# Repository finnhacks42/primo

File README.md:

KinderBot
=====

Contains design files and code for my version of the Primo robotic platform for young kids www.primo.io licenced under CC by-nc-sa 4.0 International
## Components
### Board
   - laser cut xxx and yyy in 3mm ply or bamboo
   - laser cut zzz in 1.5mm clear acrylic
   - 3d print 4 off zzz
   - 1 colorsense PCB
   - Arduino mega
   - HC05 serial bluetooth module
   - 16 rgb leds
   - 16 red leds

### Robot
   - Kinder surprise egg
   - laser cut zzz of 3mm ply
   - Arduino pro micro 
   - 2 gear motors 3-6V with tyres
   - HC05 serial bluetooth module
   - H-Bridge IC (sn75441one)
   - 1.1K resistor
   - 1.2K resistor
   - 2 12pin female header
   - 2 2pin male header
   - Battery holder for 4xAA

## Pairing Bluetooth modules
Once you have all your components ready, the first step set up the two HC-05 bluetooth modules to automatically pair with one another when they are turned on. We do this now as it is easier to setup and debug with both Arduinos handy than when they are plugged into the board/robot. We will configure the module for the board as the master and the module for the robot as the slave. 

   1) Get a permanent marker and write S for slave on one module and M for master on the other. Do it now, trust me, otherwise you will configure them and then forget which is which.
   2) Using the Arduino pro-micro for your bot, construct the circuit below on a breadboard.

Note that different manufacturers of the HC-05 breakout boards have used slightly different variants of pin orderings. On my board they `key` pin is not broken out. To temporally pull it high while programming the chip in AT mode I have just wedged a jumper wire under the protective plastic coating. Alternatively you can solder a wire directly to the pad on the bluetooth chip (see image below).

   3) Load the [bluetooth setup script](/code/bluetooth/bluetoothSetup/bluetoothSetup.ino) onto the arduino and open the serial monitor. If all goes well you should get an output like this:
   
   4) Copy the address of the slave into a text editor and replace all : with ,
   
   5) Unplug the arduino and swap the position of the master and slave modules. Edit the bluetooth setup script to setup the master module and re-upload the script to the arduino. Again if all goes well you should see ...
   
### Debugging
The bluetooth modules are setup by first putting them in AT mode and then sending AT commands to configure them. The script simply sends AT commands from the Arduino to the bluetooth module. If the steps above did not work ...
   1) Check if the module is in AT mode. If the module being configured (the one closest to the breadboard) is sucessfully in AT mode it should be flashing slowly ~ once per second when powered. If both modules are flashing rapidly, double check the wiring to the key pin. Ensure that the key pin is connected before you power up the module. 
   2) If the module is flashing slowly but you get nothing back from the AT commands check that RX/TX are wired correctly. TX0 on the arduino should be connected to RX on the bluetooth and RX0 on the arduino to TX on the bluetooth module.
   3) If the module is flashing slowly but you get garbage printed in the serial monitor, check that you serial termial baud rate is set to 9600 and line ending to NL & CR.
   4) If the module is flashing slowly but some AT command errors try running the script again. If that fails you may have to experiment with a different sequence of AT commands see xxx for an explaination of AT codes. 

## Assembly

### Board

### Robot

## Programming & Calibration

### Board

### Robot

We now need to

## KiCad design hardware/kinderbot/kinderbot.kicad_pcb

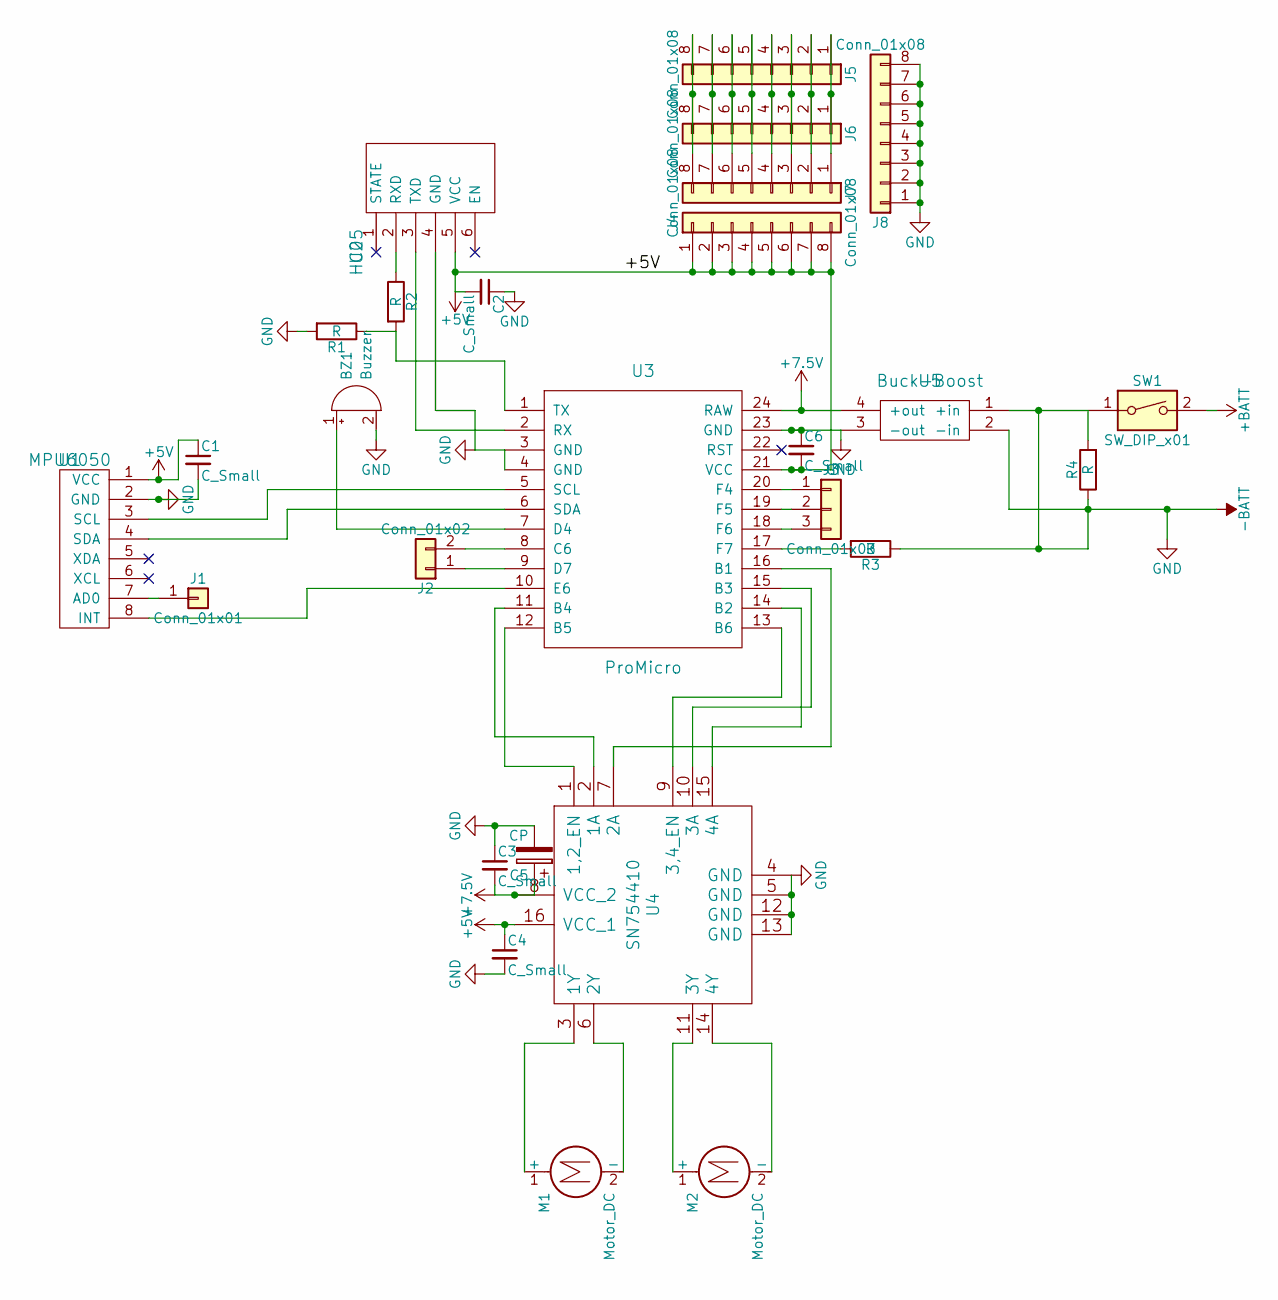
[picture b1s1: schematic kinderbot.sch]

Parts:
BZ1: Buzzer; BUZZER
C1, C2, C3, C4, C6: C_Small; CP_Radial_D4.0mm_P1.50mm
C5: CP; CP_Radial_D4.0mm_P2.00mm
J1: Conn_01x01; Pin_Header_Straight_1x01_Pitch2.54mm
J2: Conn_01x02; Pin_Header_Straight_1x02_Pitch2.54mm
J3: Conn_01x03; Pin_Header_Straight_1x03_Pitch2.54mm
J4, J5, J6, J7, J8: Conn_01x08; Pin_Header_Straight_1x08_Pitch2.54mm
M1, M2: Motor_DC; Pin_Header_Straight_1x02_Pitch2.54mm
R1, R2, R3, R4: R; R_Axial_DIN0207_L6.3mm_D2.5mm_P10.16mm_Horizontal
SW1: SW_DIP_x01; Pin_Header_Straight_1x02_Pitch2.54mm
U1: MPU6050; Pin_Header_Straight_1x08_Pitch2.54mm
U2: HC05; Pin_Header_Straight_1x06_Pitch2.54mm
U3: ProMicro
U4: SN754410; DIP-16_W7.62mm
U5: Buck-Boost; Pin_Header_Straight_2x02_Pitch2.54mm

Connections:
+5V: C1.1, C2.2, C4.1, C6.2, J4.1, J4.2, J4.3, J4.4, J4.5, J4.6, J4.7, J4.8, U1.1 (VCC), U2.5 (VCC), U3.21 (VCC), U4.16 (VCC_1)
+7.5V: C3.2, C5.1, U3.24 (RAW), U4.8 (VCC_2), U5.4 (+out)
+BATT: SW1.2
-BATT: BZ1.2 (+), C1.2, C2.1, C3.1, C4.2, C5.2, C6.1, J8.1, J8.2, J8.3, J8.4, J8.5, J8.6, J8.7, J8.8, R1.2, R3.1, R4.1, R4.2, SW1.1, U1.2 (GND), U2.4 (GND), U3.3 (GND), U3.4 (GND), U3.23 (GND), U4.4 (GND), U4.5 (GND), U4.12 (GND), U4.13 (GND), U5.1 (+in), U5.2 (-in), U5.3 (-out)
unnamed: BZ1.1 (-), U3.7 (D4)
unnamed: J1.1, U1.7 (AD0)
unnamed: J2.1, U3.9 (D7)
unnamed: J2.2, U3.8 (C6)
unnamed: J3.1, U3.20 (F4)
unnamed: J3.2, U3.19 (F5)
unnamed: J3.3, U3.18 (F6)
unnamed: J5.1, J6.1, J7.1
unnamed: J5.2, J6.2, J7.2
unnamed: J5.3, J6.3, J7.3
unnamed: J5.4, J6.4, J7.4
unnamed: J5.5, J6.5, J7.5
unnamed: J5.6, J6.6, J7.6
unnamed: J5.7, J6.7, J7.7
unnamed: J5.8, J6.8, J7.8
unnamed: M1.1 (+), U4.3 (1Y)
unnamed: M1.2 (-), U4.6 (2Y)
unnamed: M2.1 (+), U4.11 (3Y)
unnamed: M2.2 (-), U4.14 (4Y)
unnamed: R1.1, R2.2, U3.1 (TX)
unnamed: R2.1, U2.2 (RXD)
unnamed: R3.2, U3.17 (F7)
unnamed: U1.3 (SCL), U3.5 (SCL)
unnamed: U1.4 (SDA), U3.6 (SDA)
unnamed: U1.8 (INT), U3.10 (E6)
unnamed: U2.3 (TXD), U3.2 (RX)
unnamed: U3.11 (B4), U4.2 (1A)
unnamed: U3.12 (B5), U4.1 (1,2_EN)
unnamed: U3.13 (B6), U4.9 (3,4_EN)
unnamed: U3.14 (B2), U4.15 (4A)
unnamed: U3.15 (B3), U4.10 (3A)
unnamed: U3.16 (B1), U4.7 (2A)

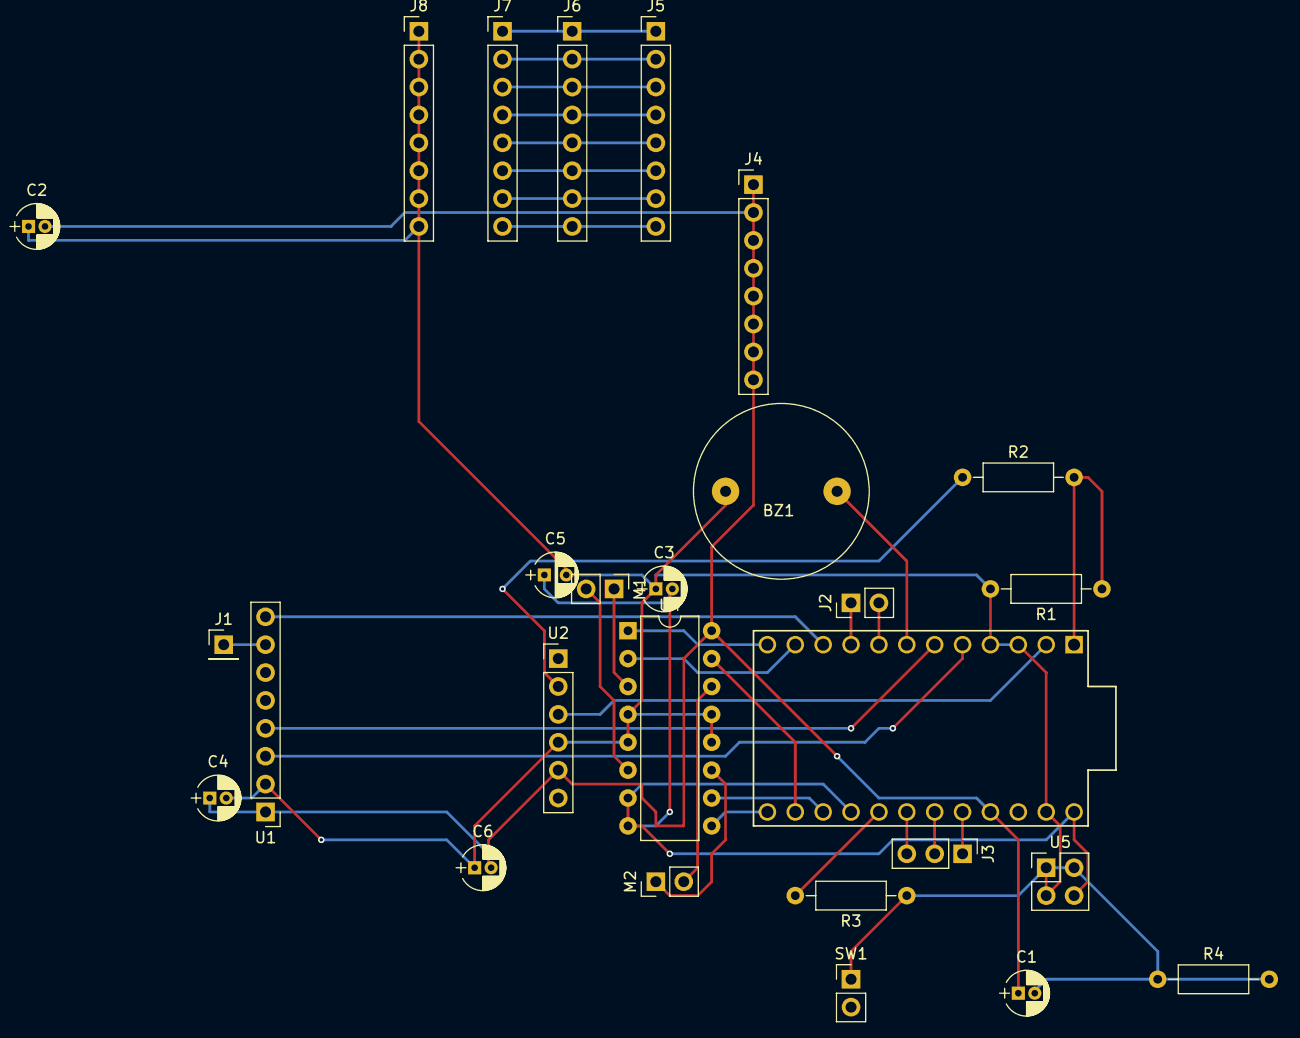
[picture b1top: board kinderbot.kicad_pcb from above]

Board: 2 copper layers, 27 parts (0 on the bottom side), 35 nets.

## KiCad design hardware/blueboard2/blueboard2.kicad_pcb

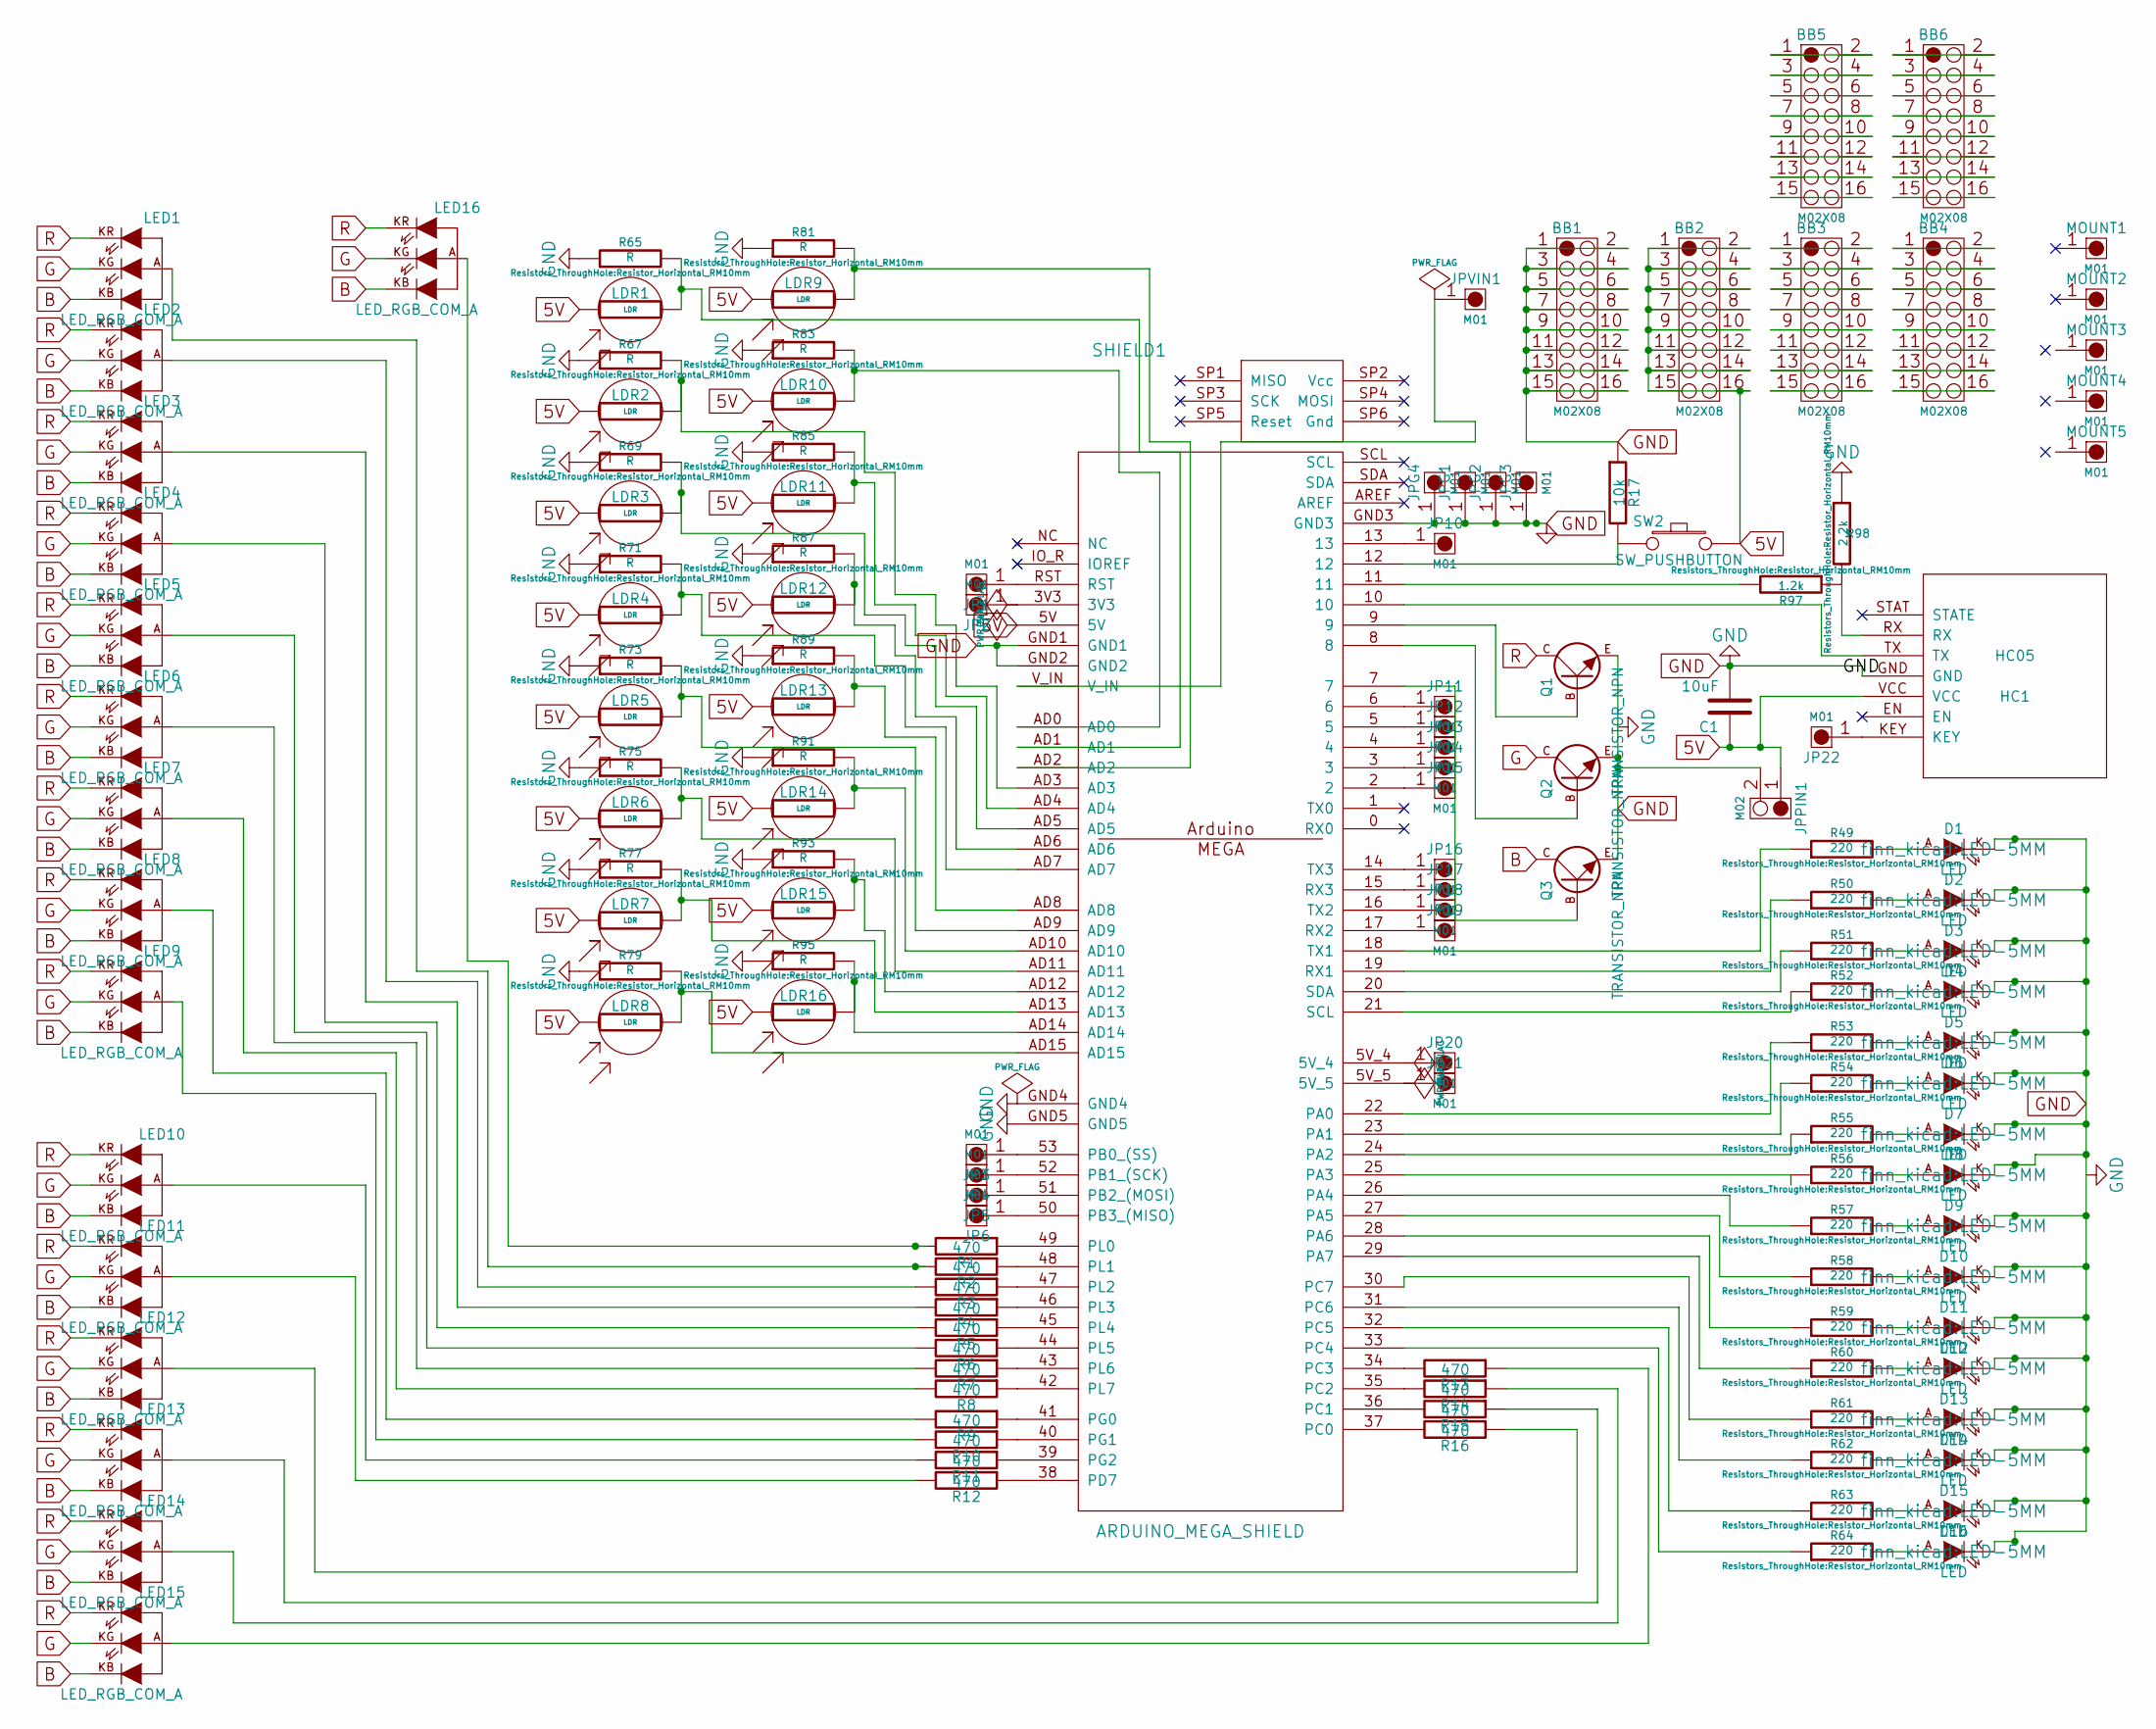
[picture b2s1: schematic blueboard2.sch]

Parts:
BB1, BB2, BB3, BB4, BB5, BB6: M02X08; 2X8
C1: 10uF; CAP_ELECTRO_D4S1.8
D1, D2, D3, D4, D5, D6, D7, D8, D9, D10, D11, D12, D13, D14, D15, D16: LED; LED-5MM
HC1: HC05
JP1, JP2, JP3, JP4, JP5, JP6, JP10, JP11, JP12, JP13, JP14, JP15, JP16, JP17, JP18, JP19, JP20, JP21, JP22: M01; 1X01
JPG1, JPG2, JPG3, JPG4: M01; 1X01
JPPIN1: M02; 1X02
JPVIN1: M01; 1X01
LDR1, LDR2, LDR3, LDR4, LDR5, LDR6, LDR7, LDR8, LDR9, LDR10, LDR11, LDR12, LDR13, LDR14, LDR15, LDR16: LDR; Resistor_Horizontal_RM15mm
LED1, LED2, LED3, LED4, LED5, LED6, LED7, LED8, LED9, LED10, LED11, LED12, LED13, LED14, LED15, LED16: LED_RGB_COM_A; LED-RGB-comA-5MM
MOUNT1, MOUNT2, MOUNT3, MOUNT4, MOUNT5: M01; SolderWirePad_single_2mmDrill
Q1, Q2, Q3: TRANSISTOR_NPN; EBC-transistor-NPN
R1, R2, R3, R4, R5, R6, R7, R8, R9, R10, R11, R12, R13, R14, R15, R16: 470; Resistor_Horizontal_RM10mm
R17: 10k; Resistor_Horizontal_RM10mm
R49, R50, R51, R52, R53, R54, R55, R56, R57, R58, R59, R60, R61, R62, R63, R64: 220; Resistor_Horizontal_RM10mm
R65, R67, R69, R71, R73, R75, R77, R79, R81, R83, R85, R87, R89, R91, R93, R95: R; Resistor_Horizontal_RM10mm
R97: 1.2k; Resistor_Horizontal_RM10mm
R98: 2.2k; Resistor_Horizontal_RM10mm
SHIELD1: ARDUINO_MEGA_SHIELD
SW2: SW_PUSHBUTTON; 1X02

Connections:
5V: BB2.1, BB2.2, BB2.3, BB2.4, BB2.5, BB2.6, BB2.7, BB2.8, BB2.9, BB2.10, BB2.11, BB2.12, BB2.13, BB2.14, BB2.15, BB2.16, C1.1, HC1.VCC, JPPIN1.1, LDR1.1, LDR2.1, LDR3.1, LDR4.1, LDR5.1, LDR6.1, LDR7.1, LDR8.1, LDR9.1, LDR10.1, LDR11.1, LDR12.1, LDR13.1, LDR14.1, LDR15.1, LDR16.1, SHIELD1.5V, SW2.2
B: LED1.KB, LED2.KB, LED3.KB, LED4.KB, LED5.KB, LED6.KB, LED7.KB, LED8.KB, LED9.KB, LED10.KB, LED11.KB, LED12.KB, LED13.KB, LED14.KB, LED15.KB, LED16.KB, Q3.C
G: LED1.KG, LED2.KG, LED3.KG, LED4.KG, LED5.KG, LED6.KG, LED7.KG, LED8.KG, LED9.KG, LED10.KG, LED11.KG, LED12.KG, LED13.KG, LED14.KG, LED15.KG, LED16.KG, Q2.C
GND: BB1.1, BB1.2, BB1.3, BB1.4, BB1.5, BB1.6, BB1.7, BB1.8, BB1.9, BB1.10, BB1.11, BB1.12, BB1.13, BB1.14, BB1.15, BB1.16, C1.2, D1.K, D2.K, D3.K, D4.K, D5.K, D6.K, D7.K, D8.K, D9.K, D10.K, D11.K, D12.K, D13.K, D14.K, D15.K, D16.K, HC1.GND, JPG1.1, JPG2.1, JPG3.1, JPG4.1, JPPIN1.2, Q1.E, Q2.E, Q3.E, R17.1, R65.1, R67.1, R69.1, R71.1, R73.1, R75.1, R77.1, R79.1, R81.1, R83.1, R85.1, R87.1, R89.1, R91.1, R93.1, R95.1, R98.1, SHIELD1.GND1, SHIELD1.GND2, SHIELD1.GND3, SHIELD1.GND4, SHIELD1.GND5
unnamed: BB3.1, BB3.2
unnamed: BB3.3, BB3.4
unnamed: BB3.5, BB3.6
unnamed: BB3.7, BB3.8
unnamed: BB3.9, BB3.10
unnamed: BB3.11, BB3.12
unnamed: BB3.13, BB3.14
unnamed: BB3.15, BB3.16
unnamed: BB4.1, BB4.2
unnamed: BB4.3, BB4.4
unnamed: BB4.5, BB4.6
unnamed: BB4.7, BB4.8
unnamed: BB4.9, BB4.10
unnamed: BB4.11, BB4.12
unnamed: BB4.13, BB4.14
unnamed: BB4.15, BB4.16
unnamed: BB5.1, BB5.2
unnamed: BB5.3, BB5.4
unnamed: BB5.5, BB5.6
unnamed: BB5.7, BB5.8
unnamed: BB5.9, BB5.10
unnamed: BB5.11, BB5.12
unnamed: BB5.13, BB5.14
unnamed: BB5.15, BB5.16
unnamed: BB6.1, BB6.2
unnamed: BB6.3, BB6.4
unnamed: BB6.5, BB6.6
unnamed: BB6.7, BB6.8
unnamed: BB6.9, BB6.10
unnamed: BB6.11, BB6.12
unnamed: BB6.13, BB6.14
unnamed: BB6.15, BB6.16
unnamed: D1.A, R49.2
unnamed: D2.A, R50.2
unnamed: D3.A, R51.2
unnamed: D4.A, R52.2
unnamed: D5.A, R53.2
unnamed: D6.A, R54.2
unnamed: D7.A, R55.2
unnamed: D8.A, R56.2
unnamed: D9.A, R57.2
unnamed: D10.A, R58.2
unnamed: D11.A, R59.2
unnamed: D12.A, R60.2
unnamed: D13.A, R61.2
unnamed: D14.A, R62.2
unnamed: D15.A, R63.2
unnamed: D16.A, R64.2
unnamed: HC1.KEY, JP22.1
unnamed: HC1.RX, R97.1, R98.2
unnamed: HC1.TX, SHIELD1.10
unnamed: JP1.1, SHIELD1.RST
unnamed: JP2.1, SHIELD1.3V3
unnamed: JP3.1, SHIELD1.53 (PB0_(SS))
unnamed: JP4.1, SHIELD1.52 (PB1_(SCK))
unnamed: JP5.1, SHIELD1.51 (PB2_(MOSI))
unnamed: JP6.1, SHIELD1.50 (PB3_(MISO))
unnamed: JP10.1, SHIELD1.13
unnamed: JP11.1, SHIELD1.6
unnamed: JP12.1, SHIELD1.5
unnamed: JP13.1, SHIELD1.4
unnamed: JP14.1, SHIELD1.3
unnamed: JP15.1, SHIELD1.2
unnamed: JP16.1, SHIELD1.14 (TX3)
unnamed: JP17.1, SHIELD1.15 (RX3)
unnamed: JP18.1, SHIELD1.16 (TX2)
unnamed: JP19.1, SHIELD1.17 (RX2)
unnamed: JP20.1, SHIELD1.5V_4
unnamed: JP21.1, SHIELD1.5V_5
unnamed: JPVIN1.1, SHIELD1.V_IN
unnamed: LDR1.2, R65.2, SHIELD1.AD1
unnamed: LDR2.2, R67.2, SHIELD1.AD3
unnamed: LDR3.2, R69.2, SHIELD1.AD5
unnamed: LDR4.2, R71.2, SHIELD1.AD7
unnamed: LDR5.2, R73.2, SHIELD1.AD9
unnamed: LDR6.2, R75.2, SHIELD1.AD11
unnamed: LDR7.2, R77.2, SHIELD1.AD13
unnamed: LDR8.2, R79.2, SHIELD1.AD15
unnamed: LDR9.2, R81.2, SHIELD1.AD2
unnamed: LDR10.2, R83.2, SHIELD1.AD0
unnamed: LDR11.2, R85.2, SHIELD1.AD4
unnamed: LDR12.2, R87.2, SHIELD1.AD6
unnamed: LDR13.2, R89.2, SHIELD1.AD8
unnamed: LDR14.2, R91.2, SHIELD1.AD10
unnamed: LDR15.2, R93.2, SHIELD1.AD12
unnamed: LDR16.2, R95.2, SHIELD1.AD14
unnamed: LED1.A, R2.2
unnamed: LED2.A, R3.2
unnamed: LED3.A, R4.2
unnamed: LED4.A, R5.2
unnamed: LED5.A, R6.2
unnamed: LED6.A, R7.2
unnamed: LED7.A, R8.2
unnamed: LED8.A, R9.2
unnamed: LED9.A, R10.2
unnamed: LED10.A, R11.2
unnamed: LED11.A, R12.2
unnamed: LED12.A, R16.1
unnamed: LED13.A, R15.1
unnamed: LED14.A, R14.1
unnamed: LED15.A, R13.1
unnamed: LED16.A, R1.2
unnamed: Q1.B, SHIELD1.9
unnamed: Q2.B, SHIELD1.8
unnamed: Q3.B, SHIELD1.7
unnamed: R1.1, SHIELD1.49 (PL0)
unnamed: R2.1, SHIELD1.48 (PL1)
unnamed: R3.1, SHIELD1.47 (PL2)
unnamed: R4.1, SHIELD1.46 (PL3)
unnamed: R5.1, SHIELD1.45 (PL4)
unnamed: R6.1, SHIELD1.44 (PL5)
unnamed: R7.1, SHIELD1.43 (PL6)
unnamed: R8.1, SHIELD1.42 (PL7)
unnamed: R9.1, SHIELD1.41 (PG0)
unnamed: R10.1, SHIELD1.40 (PG1)
unnamed: R11.1, SHIELD1.39 (PG2)
unnamed: R12.1, SHIELD1.38 (PD7)
unnamed: R13.2, SHIELD1.34 (PC3)
unnamed: R14.2, SHIELD1.35 (PC2)
unnamed: R15.2, SHIELD1.36 (PC1)
unnamed: R16.2, SHIELD1.37 (PC0)
unnamed: R17.2, SHIELD1.12, SW2.1
unnamed: R49.1, SHIELD1.18 (TX1)
unnamed: R50.1, SHIELD1.19 (RX1)
unnamed: R51.1, SHIELD1.20 (SDA)
unnamed: R52.1, SHIELD1.21 (SCL)
unnamed: R53.1, SHIELD1.22 (PA0)
unnamed: R54.1, SHIELD1.23 (PA1)
unnamed: R55.1, SHIELD1.24 (PA2)
unnamed: R56.1, SHIELD1.25 (PA3)
unnamed: R57.1, SHIELD1.26 (PA4)
unnamed: R58.1, SHIELD1.27 (PA5)
unnamed: R59.1, SHIELD1.28 (PA6)
unnamed: R60.1, SHIELD1.29 (PA7)
unnamed: R61.1, SHIELD1.30 (PC7)
unnamed: R62.1, SHIELD1.31 (PC6)
unnamed: R63.1, SHIELD1.32 (PC5)
unnamed: R64.1, SHIELD1.33 (PC4)
unnamed: R97.2, SHIELD1.11
R: LED1.KR, LED2.KR, LED3.KR, LED4.KR, LED5.KR, LED6.KR, LED7.KR, LED8.KR, LED9.KR, LED10.KR, LED11.KR, LED12.KR, LED13.KR, LED14.KR, LED15.KR, LED16.KR, Q1.C

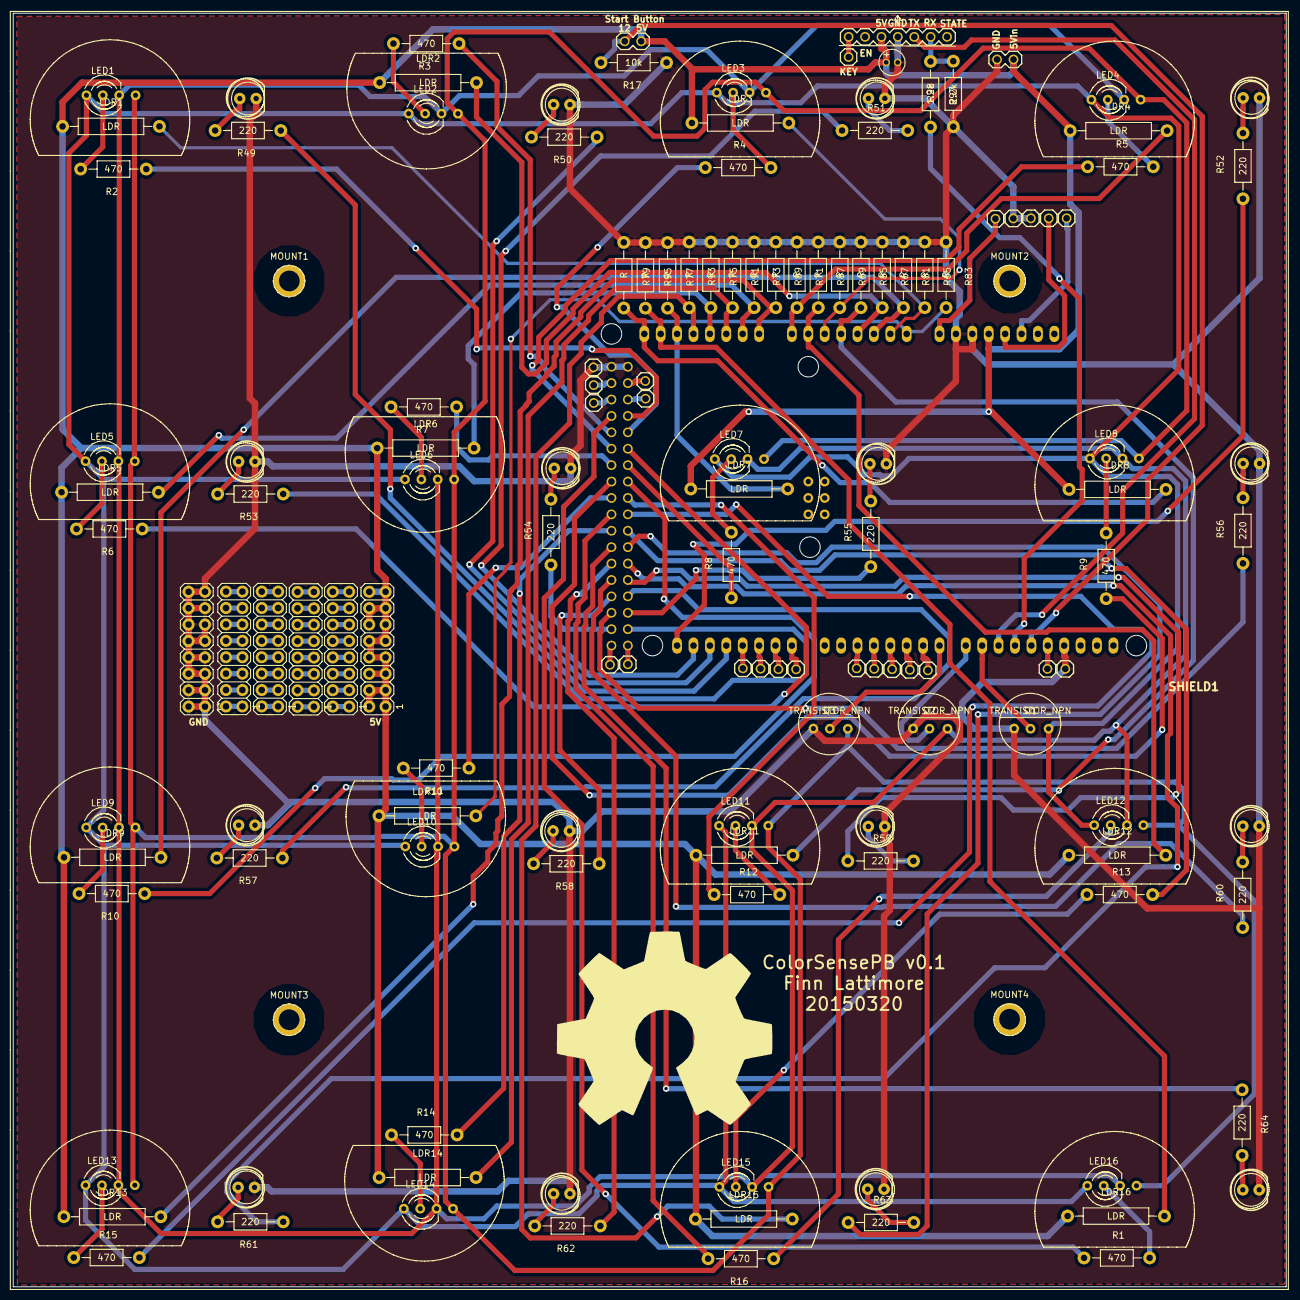
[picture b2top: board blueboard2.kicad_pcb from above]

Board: 2 copper layers, 197.1 x 197.2 mm, 143 parts (1 on the bottom side), 144 nets.

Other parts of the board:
LOGO1, LOGO2: LOGO; OSWH_LOGO

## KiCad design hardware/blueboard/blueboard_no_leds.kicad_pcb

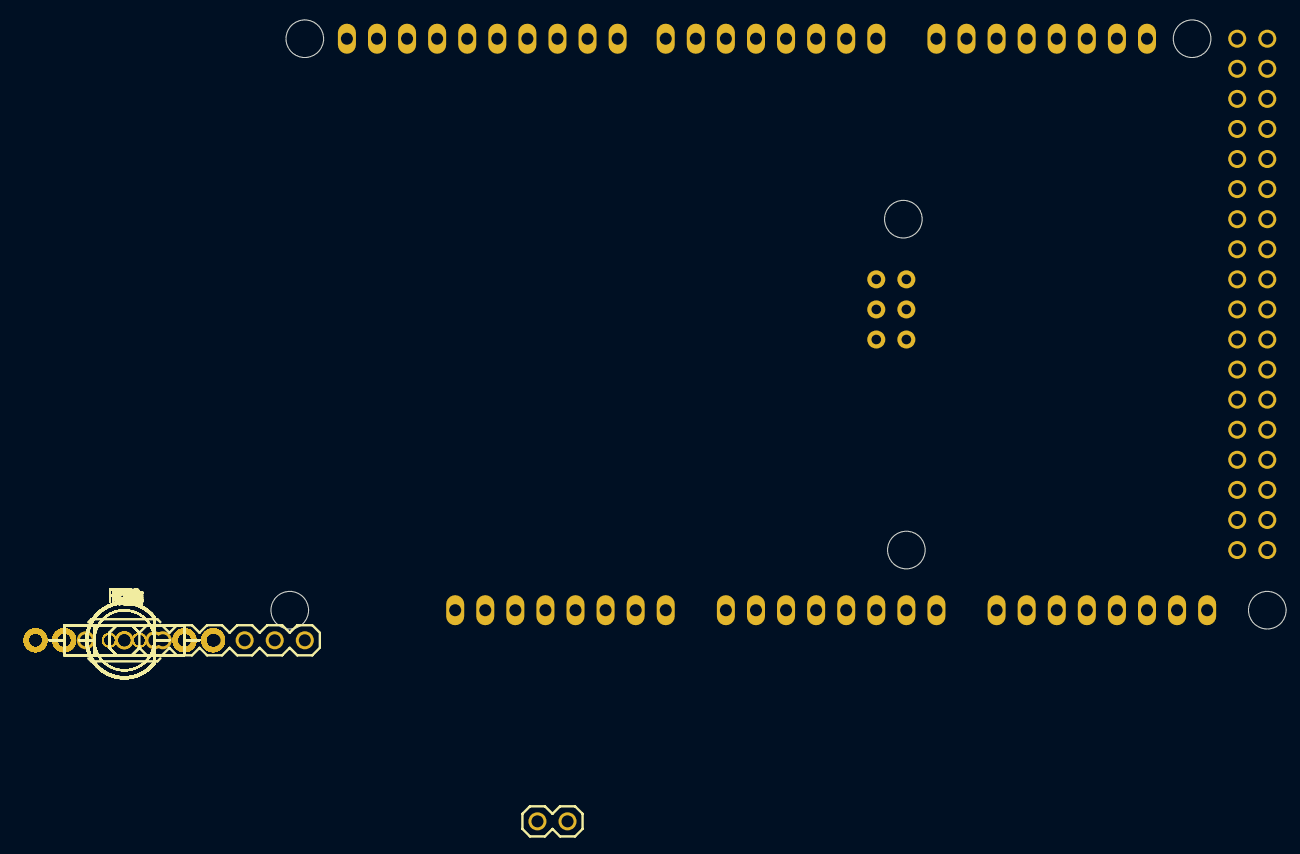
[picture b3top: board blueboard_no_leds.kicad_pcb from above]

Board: 2 copper layers, 71 parts (0 on the bottom side), 56 nets, no tracks yet.

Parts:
BT1: BATTERY; 1X02
D1, D2, D3, D4, D5, D6, D7, D8, D9, D10, D11, D12, D13, D14, D15, D16: LED; LED-5MM
JP1: M01; 1X01
JP2: M07; 1X07
R1, R3, R5, R7, R9, R11, R13, R15, R17, R19, R21, R23, R25, R27, R29, R31: R; Resistor_Horizontal_RM10mm
R2, R4, R6, R8, R10, R12, R14, R16, R18, R20, R22, R24, R26, R28, R30, R32: RES_PHOTO_LDR; Resistor_Horizontal_RM15mm
R33: 1.2k; Resistor_Horizontal_RM10mm
R34: 2.2k; Resistor_Horizontal_RM15mm
R35, R36, R37, R38, R39, R40, R41, R42, R43, R44, R45, R46, R47, R48, R49, R50: 220; Resistor_Horizontal_RM10mm
SHIELD1: ARDUINO_MEGA_SHIELD
SW1: SW_SPST; SW_PUSHBUTTON_TC0122

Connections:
5V: JP2.3, R2.1, R4.1, R6.1, R8.1, R10.1, R12.1, R14.1, R16.1, R18.1, R20.1, R22.1, R24.1, R26.1, R28.1, R30.1, R32.1, SHIELD1.5V
GND: BT1.2, D1.K, D2.K, D3.K, D4.K, D5.K, D6.K, D7.K, D8.K, D9.K, D10.K, D11.K, D12.K, D13.K, D14.K, D15.K, D16.K, JP2.4, R1.1, R3.1, R5.1, R7.1, R9.1, R11.1, R13.1, R15.1, R17.1, R19.1, R21.1, R23.1, R25.1, R27.1, R29.1, R31.1, R34.2, SHIELD1.GND1, SHIELD1.GND2, SHIELD1.GND3, SHIELD1.GND4, SHIELD1.GND5
unnamed: BT1.1, SW1.2
unnamed: D1.A, R35.2
unnamed: D2.A, R36.2
unnamed: D3.A, R37.2
unnamed: D4.A, R38.2
unnamed: D5.A, R39.2
unnamed: D6.A, R40.2
unnamed: D7.A, R41.2
unnamed: D8.A, R42.2
unnamed: D9.A, R43.2
unnamed: D10.A, R44.2
unnamed: D11.A, R45.2
unnamed: D12.A, R46.2
unnamed: D13.A, R47.2
unnamed: D14.A, R48.2
unnamed: D15.A, R49.2
unnamed: D16.A, R50.2
unnamed: JP1.1, JP2.1
unnamed: JP2.5, R33.1, R34.1
unnamed: JP2.6, SHIELD1.10
unnamed: R1.2, R2.2, SHIELD1.AD1
unnamed: R3.2, R4.2, SHIELD1.AD3
unnamed: R5.2, R6.2, SHIELD1.AD5
unnamed: R7.2, R8.2, SHIELD1.AD7
unnamed: R9.2, R10.2, SHIELD1.AD9
unnamed: R11.2, R12.2, SHIELD1.AD11
unnamed: R13.2, R14.2, SHIELD1.AD13
unnamed: R15.2, R16.2, SHIELD1.AD15
unnamed: R17.2, R18.2, SHIELD1.AD2
unnamed: R19.2, R20.2, SHIELD1.AD0
unnamed: R21.2, R22.2, SHIELD1.AD4
unnamed: R23.2, R24.2, SHIELD1.AD6
unnamed: R25.2, R26.2, SHIELD1.AD8
unnamed: R27.2, R28.2, SHIELD1.AD10
unnamed: R29.2, R30.2, SHIELD1.AD12
unnamed: R31.2, R32.2, SHIELD1.AD14
unnamed: R33.2, SHIELD1.11
unnamed: R35.1, SHIELD1.18
unnamed: R36.1, SHIELD1.19
unnamed: R37.1, SHIELD1.20
unnamed: R38.1, SHIELD1.21
unnamed: R39.1, SHIELD1.22
unnamed: R40.1, SHIELD1.23
unnamed: R41.1, SHIELD1.24
unnamed: R42.1, SHIELD1.25
unnamed: R43.1, SHIELD1.26
unnamed: R44.1, SHIELD1.27
unnamed: R45.1, SHIELD1.28
unnamed: R46.1, SHIELD1.29
unnamed: R47.1, SHIELD1.30
unnamed: R48.1, SHIELD1.31
unnamed: R49.1, SHIELD1.32
unnamed: R50.1, SHIELD1.33
VCC: SHIELD1.V_IN, SW1.1

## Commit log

2014-12-01 adds svg degin files for board
2014-12-01 enlarges space for resistor in programming tiles
2014-12-19 adds primo board code with median calculation. There is a bug in array access
2014-12-20 creates directory structure and adds code scripts for testing bluetooth communication
2014-12-20 gets primoboard codeto the point where leds light when tiles are inserted, code is executed when button is pushed and leds indicate which opperation is currently being executed. instruction execution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
2014-12-21 updates promoboard to where I thought it was on last commit
2014-12-21 adds first version of code for robot - just recieves instructions from board over bluetooth and prints them to Serial
2015-02-05 lots of changes
2015-02-14 too many changes to remember
2015-02-14 state when board was cncd
2015-02-22 prior to starting over on cnc board
2015-03-19 round 2 of board design
2015-03-21 state when board sent to manufacture
2015-05-04 updated svgs to fit manufactured board. Reconnected resistors in schematica
2015-05-04 adds code to test pcb from arduino sketchbook
2015-10-23 updates to printed circuit board. Still missing programming access, switch mount and charging access
2015-11-07 changes from old laptop
2015-11-07 fixes indicator test so LEDs come on in board order
2015-11-07 Updates RGBLEDTest to pins for printed PCB
2015-11-07 adds LDRTest, configured for printed pcb
2015-11-07 adds README for board callibration
2015-11-21 moves some common code to utils
2015-11-24 completes refactor of readdata.py and utils.py to avoid use of numpy/scipy
2015-11-24 removed old files
2015-11-24 moves things into a more logical directory structure
2018-04-01 updates board svg top to have tiles go all the same direction
2018-04-01 makes square pegs for board holder to glue in
2018-04-02 removes double cut from tiles in second row
2018-04-02 splits board design into 600 by 400 mm sheets
2018-04-11 adds .csv to gitignore
2018-04-11 adds bottom half of tile smaller than hole dimension
2018-04-11 adds cutout for switch and power in
2018-04-11 improves design to attach bottom of board
2018-04-11 adds version of board with cross support for pcb
2018-04-11 cleans up board design files
2018-04-11 cleans up svgs for robot
2018-04-13 completes robot design, adds cross support for pcb
2018-04-13 major updates to color sensing code
2018-04-15 moves axel back
2018-04-15 removes cable port
2018-04-15 moves mount point for kinder backward
2018-04-15 fixes cutout for switch
2018-04-15 adds script to test wheels on robot
2018-04-17 adds arduino sketch to pair hc05 bluetooth modules
2018-04-17 starts on docs, cleans up old stuff
2018-04-17 resizes images
2019-12-08 adds README for board setup
2019-12-08 cleans up board code
2019-12-08 cleans up notebook
2019-12-08 updates to include arduino code generation in read.py
2019-12-08 updates README
2019-12-08 local changes made oh so long ago
2019-12-08 adds initial readme for the robot section
